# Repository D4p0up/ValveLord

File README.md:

# ValveLord
Tube Overdrive schematic and PCB inspired by famous 12AU7 Valvecaster

Design fits into a 1590B case.

Designed with Kicad, Mock-up projected with Freecad 

[demo video](https://github.com/D4p0up/ValveLord/blob/main/2021-05-22%2015-44-17.mp4)

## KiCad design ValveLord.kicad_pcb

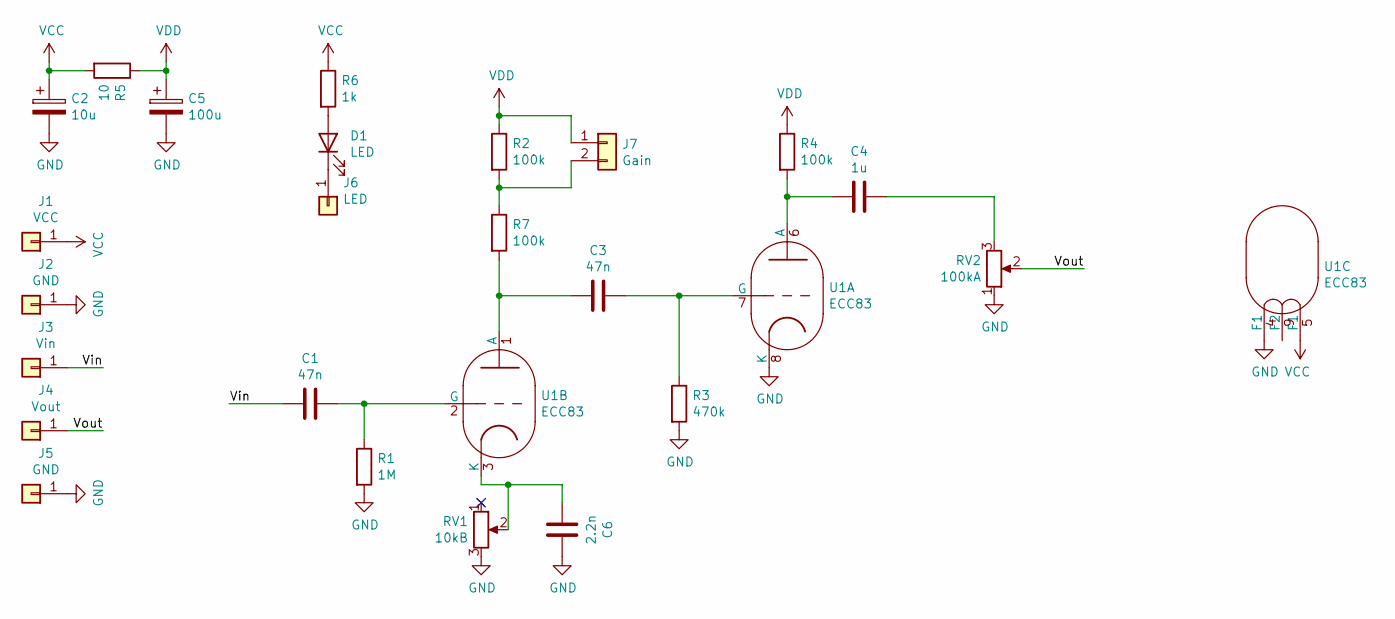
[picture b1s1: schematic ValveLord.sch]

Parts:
C1, C3: 47n; C_0805_2012Metric_Pad1.18x1.45mm_HandSolder
C2: 10u; CP_Radial_D5.0mm_P2.50mm
C4: 1u; C_0805_2012Metric_Pad1.18x1.45mm_HandSolder
C5: 100u; CP_Radial_D5.0mm_P2.50mm
C6: 2.2n; C_0805_2012Metric_Pad1.18x1.45mm_HandSolder
D1: LED; LED_D3.0mm
J1: VCC; PinSocket_1x01_P2.54mm_Vertical
J2, J5: GND; PinSocket_1x01_P2.54mm_Vertical
J3: Vin; PinSocket_1x01_P2.54mm_Vertical
J4: Vout; PinSocket_1x01_P2.54mm_Vertical
J6: LED; PinSocket_1x01_P2.54mm_Vertical
J7: Gain; PinSocket_1x02_P2.54mm_Vertical
R1: 1M; R_0805_2012Metric_Pad1.20x1.40mm_HandSolder
R2, R4, R7: 100k; R_0805_2012Metric_Pad1.20x1.40mm_HandSolder
R3: 470k; R_0805_2012Metric_Pad1.20x1.40mm_HandSolder
R5: 10; R_0805_2012Metric_Pad1.20x1.40mm_HandSolder
R6: 1k; R_0805_2012Metric_Pad1.20x1.40mm_HandSolder
RV1: 10kB; Potentiometer_Piher_T-16H_Single_Horizontal
RV2: 100kA; Potentiometer_Piher_T-16H_Single_Horizontal
U1: ECC83; Valve_ECC-83-1

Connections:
/Vin: C1.2, J3.1
/Vout: J4.1, RV2.2
GND: C2.2, C5.2, C6.1, J2.1, J5.1, R1.2, R3.2, RV1.3, RV2.1, U1.4 (F1), U1.8 (K)
unnamed: C1.1, R1.1, U1.2 (G)
unnamed: C3.1, R3.1, U1.7 (G)
unnamed: C3.2, R7.2, U1.1 (A)
unnamed: C4.1, RV2.3
unnamed: C4.2, R4.2, U1.6 (A)
unnamed: C6.2, RV1.2, U1.3 (K)
unnamed: D1.1 (K), J6.1
unnamed: D1.2 (A), R6.2
unnamed: J7.2, R2.2, R7.1
VCC: C2.1, J1.1, R5.2, R6.1, U1.5 (F1)
VDD: C5.1, J7.1, R2.1, R4.1, R5.1

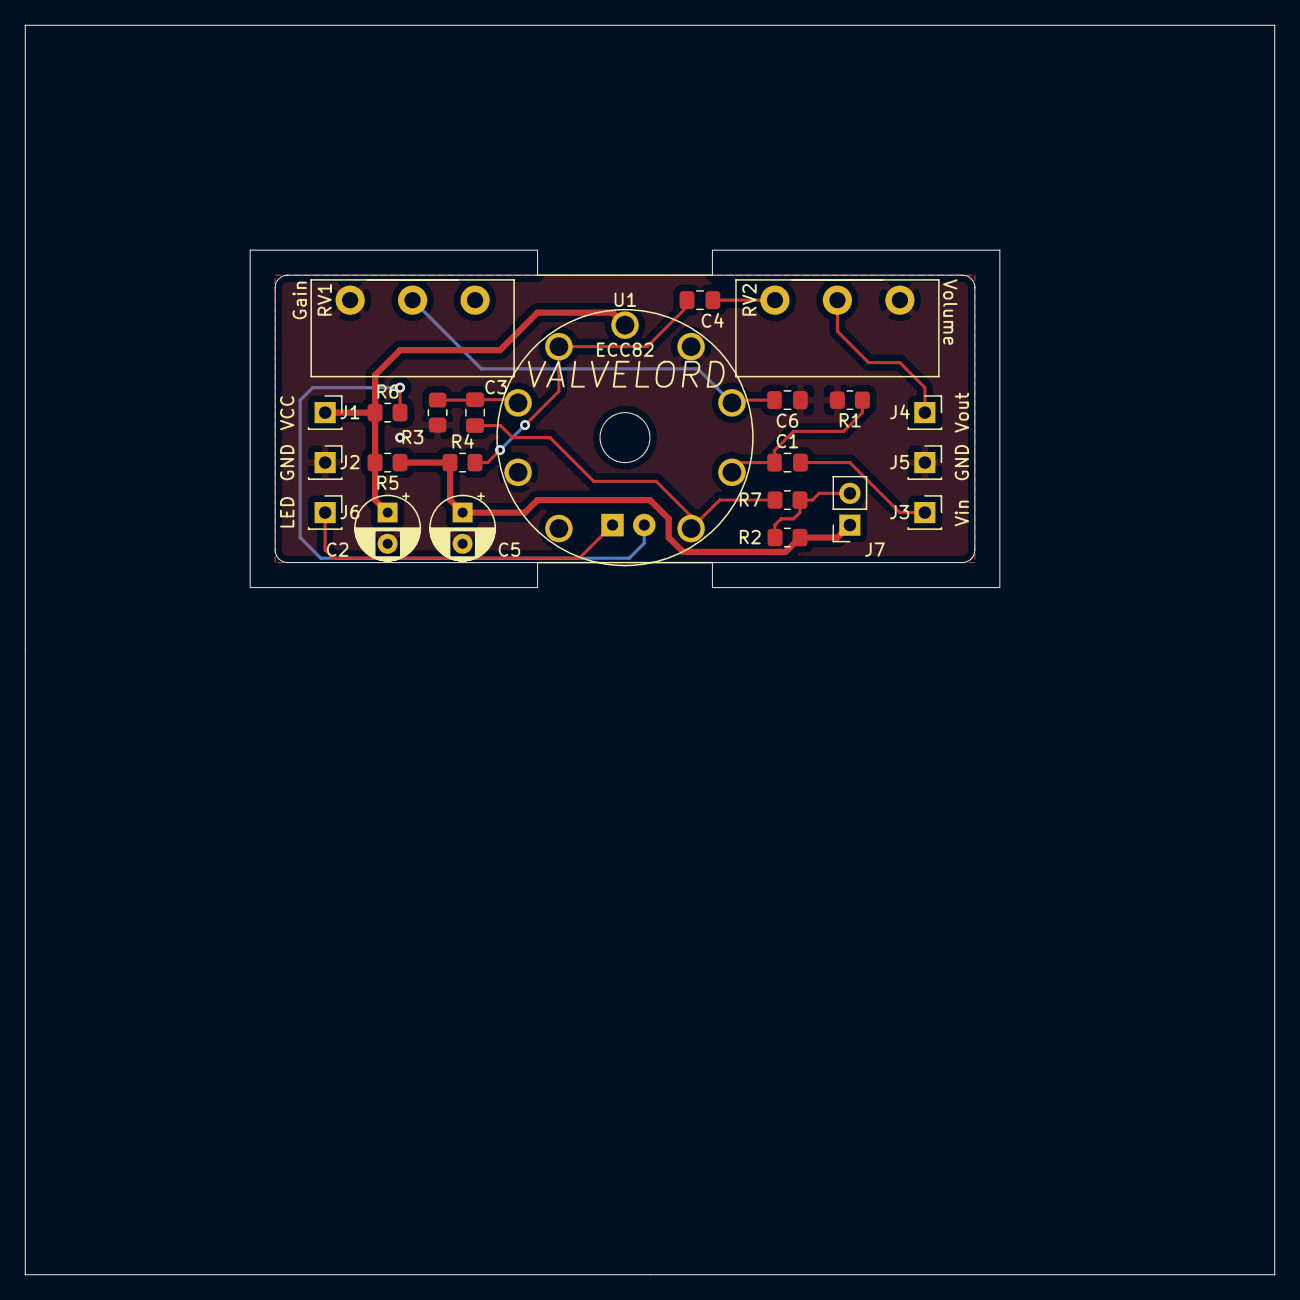
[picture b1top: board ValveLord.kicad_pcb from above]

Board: 2 copper layers, 100.0 x 100.0 mm, 24 parts (1 on the bottom side), 14 nets.

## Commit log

2021-05-23 Release 1
2021-05-23 Correcting ground Bug
2021-05-23 Added media
2021-06-08 Add files via upload
    adding images
2022-05-22 Add real image
    Add
